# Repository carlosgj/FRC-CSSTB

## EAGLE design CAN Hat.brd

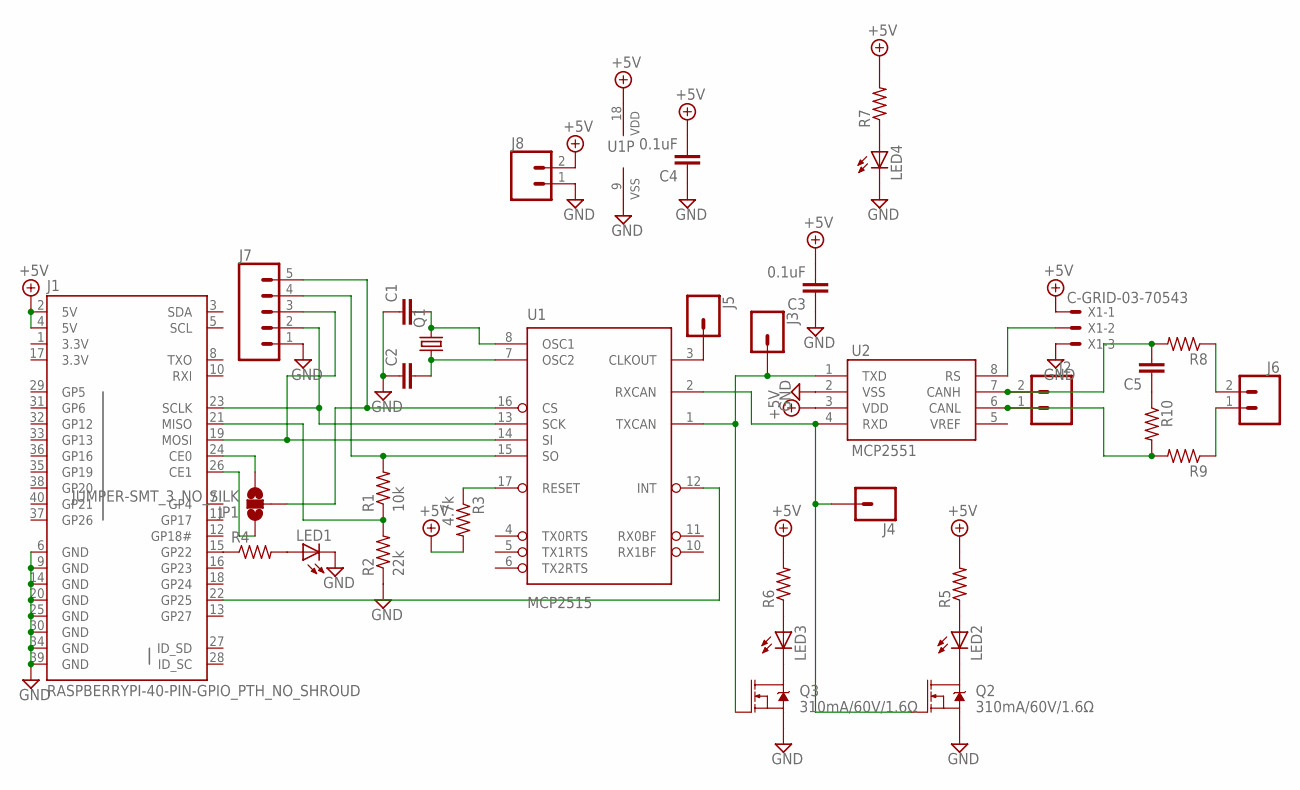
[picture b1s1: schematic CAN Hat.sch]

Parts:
C1, C2, C5: C-EUC1206; C1206
C3, C4: 0.1uF; C1206
J1: RASPBERRYPI-40-PIN-GPIO_PTH_NO_SHROUD; 2X20
J2, J6: CONN_02; 1X02
J3, J4, J5: CONN_01; 1X01
J7: CONN_05; 1X05
J8: CONN_023.5MM; SCREWTERMINAL-3.5MM-2
JP1: JUMPER-SMT_3_NO_SILK; SMT-JUMPER_3_NO_SILK
LED1, LED2, LED3, LED4: LED3MM
Q1: CRYSTALHC49U70; HC49U70
Q2, Q3: 310mA/60V/1.6Ω; SOT323
R1: 10k; R1206
R2: 22k; R1206
R3: 4.7k; R1206
R4, R5, R6, R7, R8, R9, R10: R-US_R1206; R1206
U1: MCP2515; DIP18
U2: MCP2551; SO08
X1: C-GRID-03-70543; 70543-03

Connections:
3.3V: J1.1 (3.3V), J1.17 (3.3V)
+5V: C3.2, C4.2, J1.2 (5V), J1.4 (5V), J8.2, R3.2, R5.2, R6.2, R7.2, U1.18 (VDD), U2.3 (VDD), X1.1
GND: C1.1, C2.1, C3.1, C4.1, J1.6 (GND), J1.9 (GND), J1.14 (GND), J1.20 (GND), J1.25 (GND), J1.30 (GND), J1.34 (GND), J1.39 (GND), J7.1, J8.1, LED1.K (C), LED4.K (C), Q2.2 (S), Q3.2 (S), R2.1, U1.9 (VSS), U2.2 (VSS), X1.3
unnamed: J4.1, Q2.1 (G), U1.2 (RXCAN), U2.4 (RXD)
unnamed: J3.1, Q3.1 (G), U1.1 (TXCAN), U2.1 (TXD)
unnamed: C2.2, Q1.1, U1.7 (OSC2)
unnamed: C1.2, Q1.2, U1.8 (OSC1)
unnamed: LED4.A, R7.1
unnamed: J7.5, JP1.2, U1.16 (CS)
unnamed: J1.24 (CE0), JP1.3
unnamed: J1.26 (CE1), JP1.1
unnamed: R3.1, U1.17 (RESET)
unnamed: J1.23 (SCLK), J7.2, U1.13 (SCK)
unnamed: J1.19 (MOSI), J7.3, U1.14 (SI)
unnamed: J1.21 (MISO), R1.1, R2.2
unnamed: J1.22 (GP25), U1.12 (INT)
unnamed: U2.8 (RS), X1.2
unnamed: J1.15 (GP22), R4.1
unnamed: LED1.A, R4.2
unnamed: J2.1, R9.2, R10.2, U2.6 (CANL)
unnamed: C5.2, J2.2, R8.2, U2.7 (CANH)
unnamed: LED2.K (C), Q2.3 (D)
unnamed: LED2.A, R5.1
unnamed: LED3.A, R6.1
unnamed: LED3.K (C), Q3.3 (D)
unnamed: J5.1, U1.3 (CLKOUT)
unnamed: J6.1, R9.1
unnamed: J6.2, R8.1
unnamed: J7.4, R1.2, U1.15 (SO)
unnamed: C5.1, R10.1

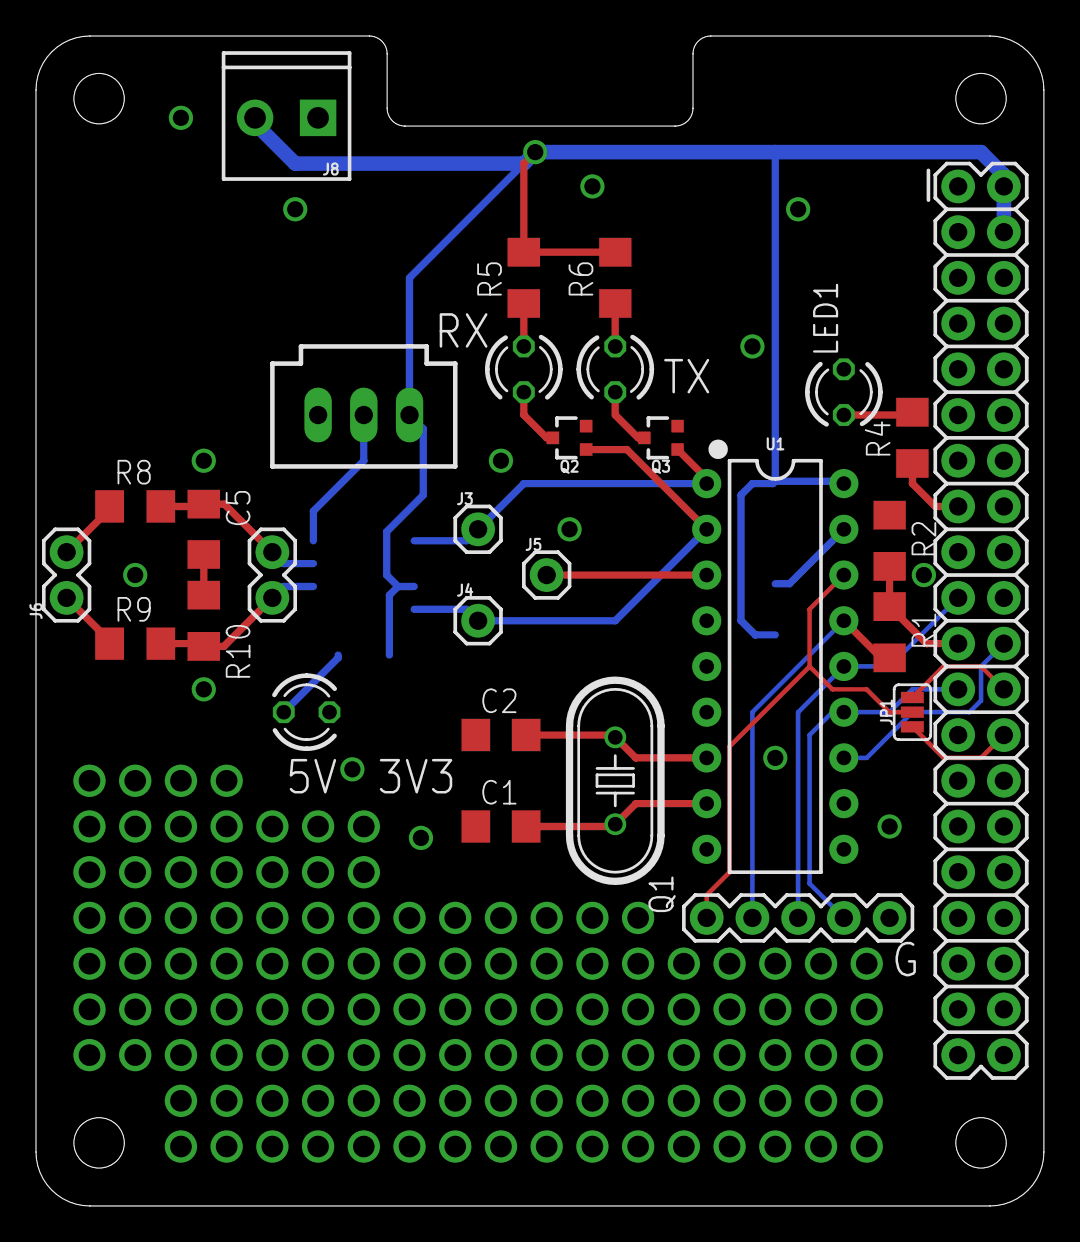
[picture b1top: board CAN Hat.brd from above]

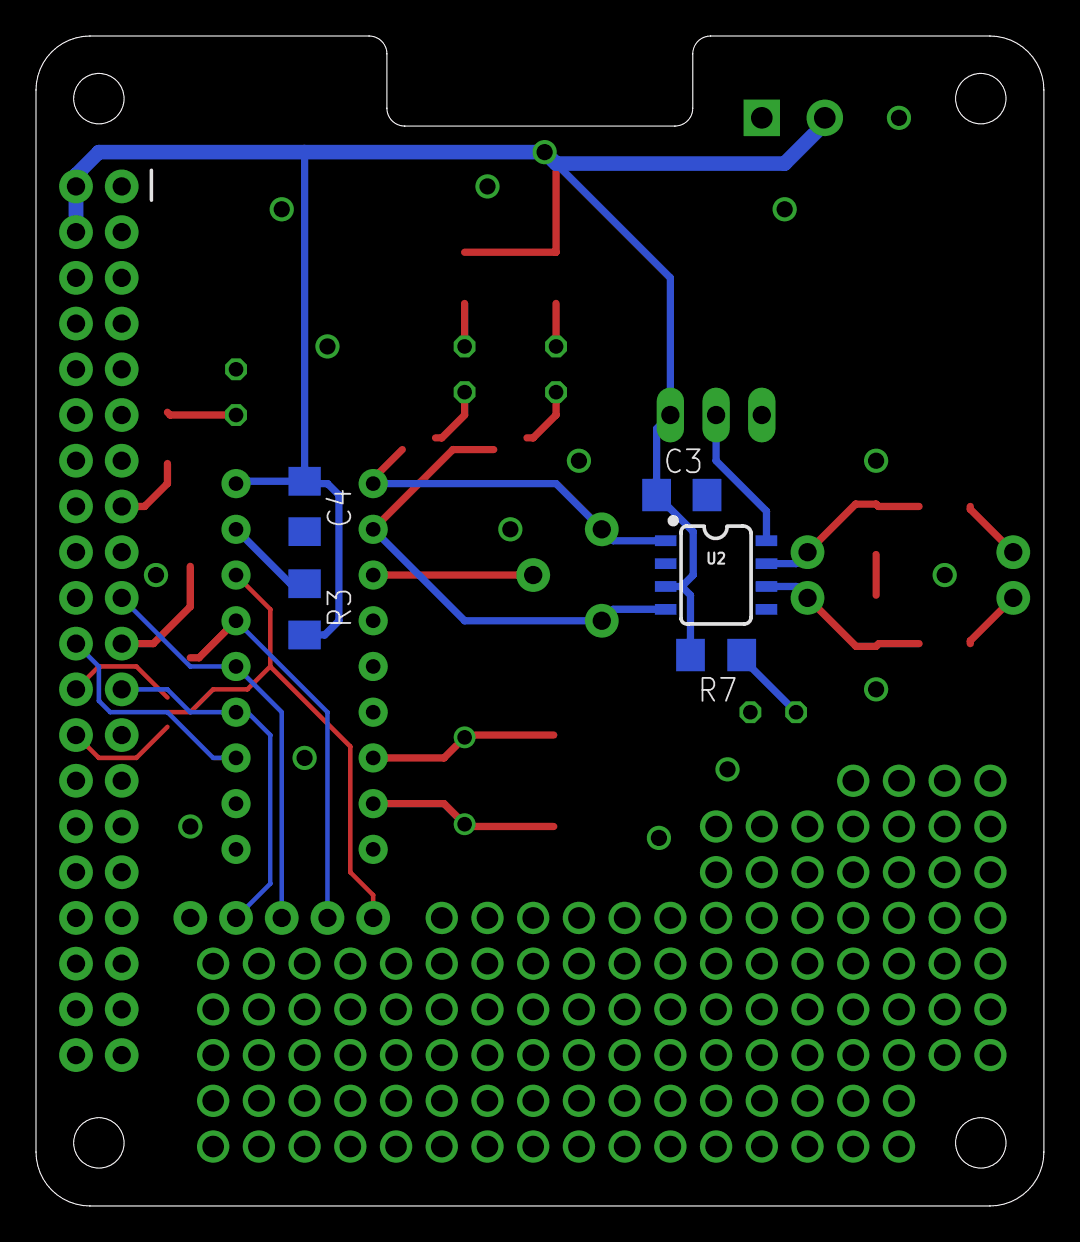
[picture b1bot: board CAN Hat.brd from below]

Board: 2 copper layers, 56.0 x 65.0 mm, 34 parts (5 on the bottom side), 30 nets.

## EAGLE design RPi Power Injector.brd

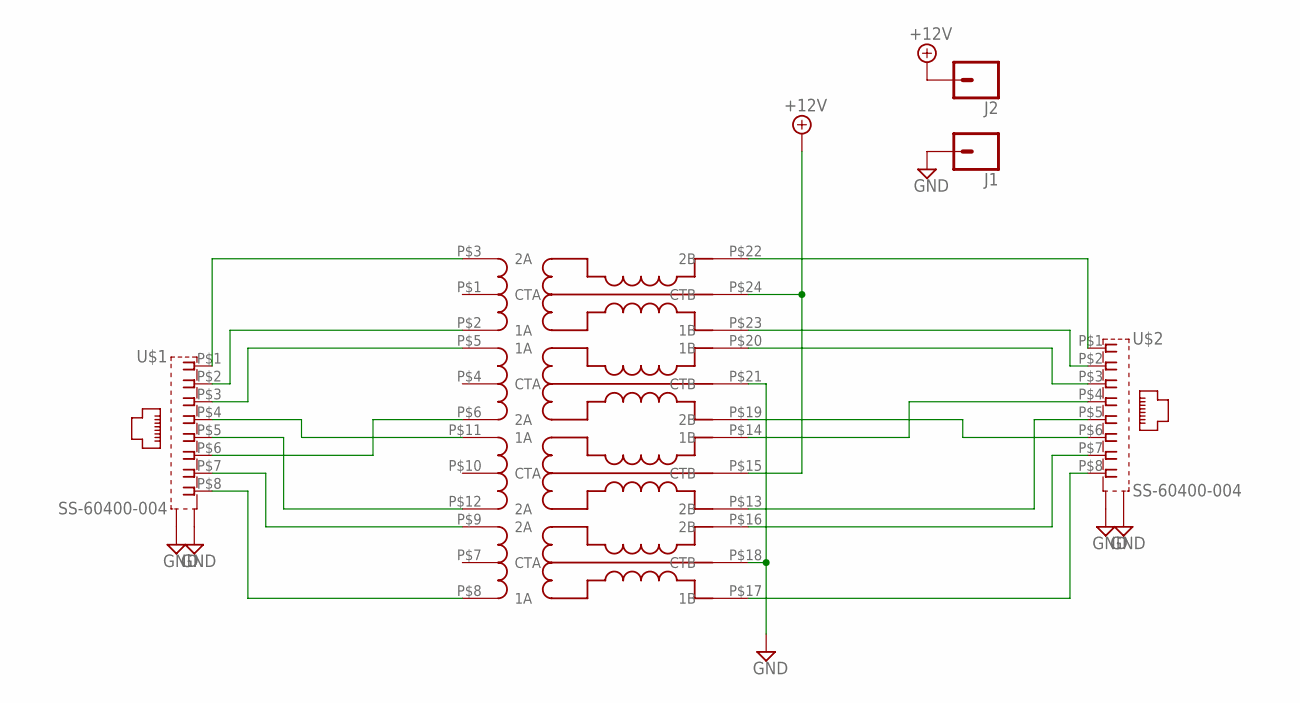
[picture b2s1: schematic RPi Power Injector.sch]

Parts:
J1, J2: CONN_01; 1X01
U$1, U$2: SS-60400-004
U$3: SM51589PEL; SOIC-24-EW

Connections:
1A_N: U$1.P$2 (2), U$3.P$2 (1A)
1A_P: U$1.P$1 (1), U$3.P$3 (2A)
1B_N: U$2.P$2 (2), U$3.P$23 (1B)
1B_P: U$2.P$1 (1), U$3.P$22 (2B)
2A_N: U$1.P$6 (6), U$3.P$6 (2A)
2A_P: U$1.P$3 (3), U$3.P$5 (1A)
2B_N: U$2.P$6 (6), U$3.P$19 (2B)
2B_P: U$2.P$3 (3), U$3.P$20 (1B)
3A_N: U$1.P$5 (5), U$3.P$12 (2A)
3A_P: U$1.P$4 (4), U$3.P$11 (1A)
3B_N: U$2.P$5 (5), U$3.P$13 (2B)
3B_P: U$2.P$4 (4), U$3.P$14 (1B)
4A_N: U$1.P$8 (8), U$3.P$8 (1A)
4A_P: U$1.P$7 (7), U$3.P$9 (2A)
4B_N: U$2.P$8 (8), U$3.P$17 (1B)
4B_P: U$2.P$7 (7), U$3.P$16 (2B)
+12V: J2.1, U$3.P$15 (CTB), U$3.P$24 (CTB)
GND: J1.1, U$1.GND@1 (S1), U$1.GND@2 (S2), U$2.GND@1 (S1), U$2.GND@2 (S2), U$3.P$18 (CTB), U$3.P$21 (CTB)

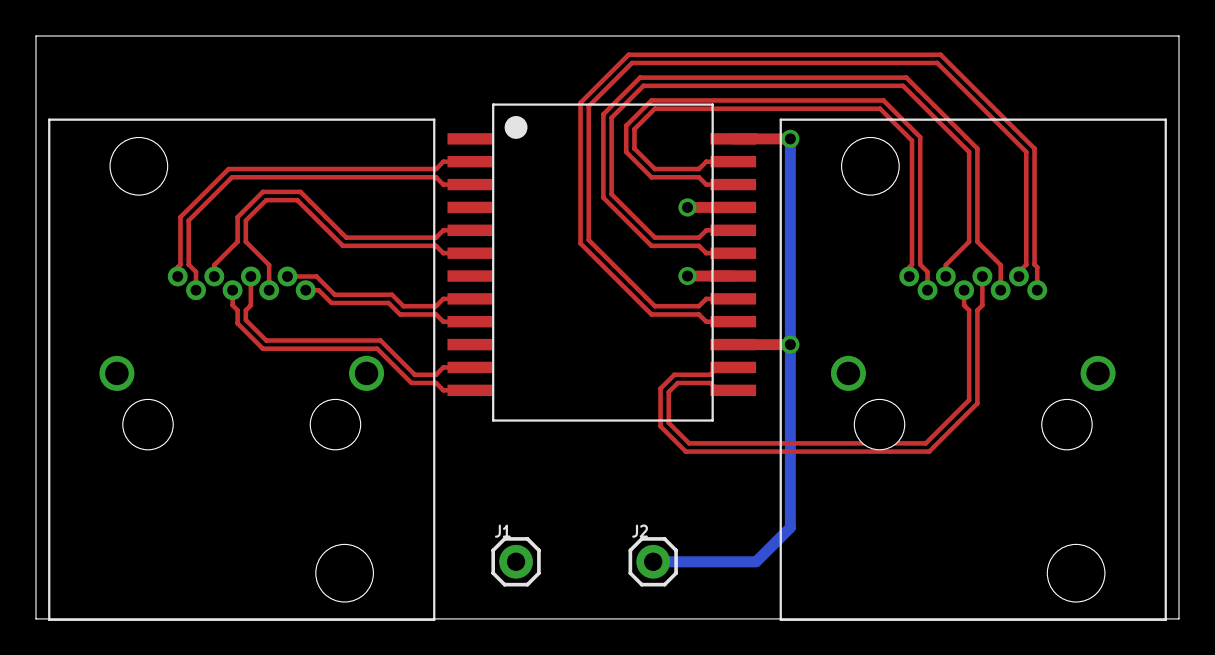
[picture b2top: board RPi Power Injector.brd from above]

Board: 2 copper layers, 63.5 x 32.4 mm, 5 parts (0 on the bottom side), 18 nets.

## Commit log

2018-11-26 Initial mechanical stuff
2019-04-02 CAN monitor PCB
2019-04-02 CAN monitor updates
2019-04-17 Core panel assembly
2019-05-06 Part 1 writeup
2019-05-06 Finished Part 1
2019-05-18 Adding Part II
2019-06-24 Adding part III
2019-06-24 Adding part IV

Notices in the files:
parts and their libraries:
SparkFun-IC-Comms: Licensing: Creative Commons ShareAlike 4.0 International - https://creativecommons.org/licenses/by-sa/4.0
